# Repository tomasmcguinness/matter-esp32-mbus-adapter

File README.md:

# Matter ESP32 M-Bus Adapter

> ⚠️ **Work in progress.** This project is under active development and is not
> finished. Nothing here should be considered stable or production-ready. Expect
> breaking changes, incomplete features and rough edges.

An ESP32-C6 adapter board for wired [M-Bus](https://en.wikipedia.org/wiki/Meter-Bus)
(EN 13757) meters, with firmware examples that expose meter readings to a
[Matter](https://csa-iot.org/all-solutions/matter/) fabric over Thread.

It is built around an **ESP32-C6** (native 802.15.4 radio) and a custom PCB that
provides the M-Bus master side: the ~36 V/~24 V bus supply, the mark/space
modulator and the receive comparator, so a meter can be connected directly to the
board's M+/M- terminals.

## Repository layout

| Path | Contents |
|---|---|
| `examples/` | Firmware examples, each a standalone ESP-IDF project — see the [examples README](examples/README.md) |
| `hardware/PCB/` | KiCad schematic, PCB layout and BOM (`PCB.csv`, Mouser part numbers) |
| `tools/pcb-test/` | Standalone GPIO-only app for bringing up the M-Bus analogue circuit — see its own [README](tools/pcb-test/README.md) |
| `tools/kamstrup-403-sim/` | Raspberry Pi Pico sketch that simulates a Kamstrup MULTICAL 403 on the bus — see its own [README](tools/kamstrup-403-sim/README.md) |

## Examples

| Example | Device | Matter device type |
|---------|--------|--------------------|
| [KamstrupMultical403](examples/matter/KamstrupMultical403) | Kamstrup MULTICAL 403 heat meter | Custom Heat Meter cluster, with Flow Measurement |

Each example's README covers building, flashing, bring-up modes and the factory
reset gesture.

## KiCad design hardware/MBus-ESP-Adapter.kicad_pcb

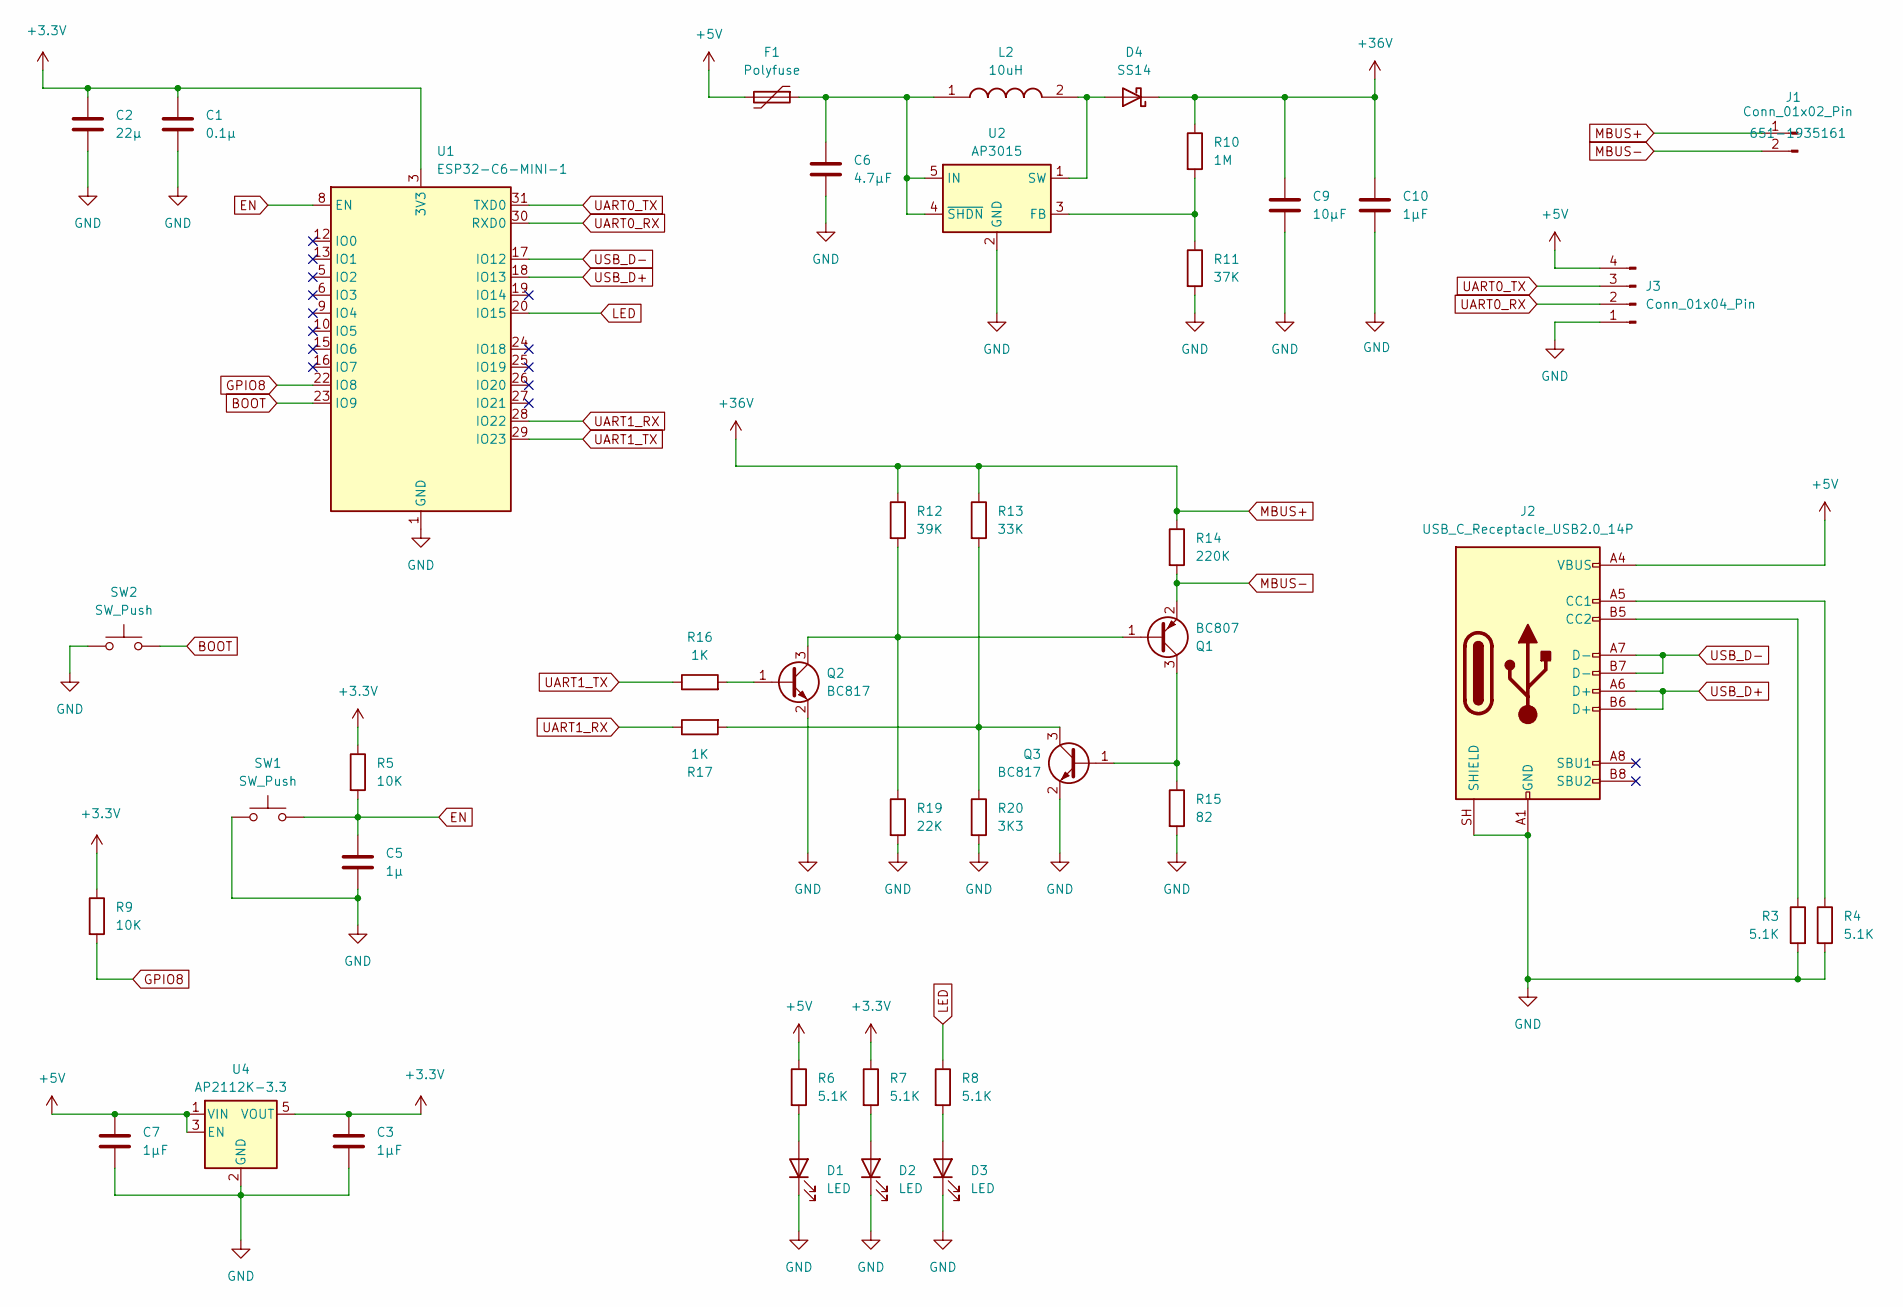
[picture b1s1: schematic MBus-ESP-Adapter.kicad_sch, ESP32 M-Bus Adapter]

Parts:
C1: 0.1µ; C_0805_2012Metric; Mouser_PN 187-CL21B104KBCNNNC
C2: 22µ; C_0805_2012Metric; Mouser_PN 963-MSASL21GBB5226MT
C3, C7: 1µF; C_0805_2012Metric; Mouser_PN 80-C0805C105J4RACLR
C5: 1µ; C_0805_2012Metric; Mouser_PN 80-C0805C105J4RACLR
C6: 4.7µF; C_1206_3216Metric; Mouser_PN 80-C1206C475K5P
C9: 10µF; C_1206_3216Metric; Mouser_PN 963-UMK316BBJ106ML-T
C10: 1µF; C_1206_3216Metric; Mouser_PN 187-CL31B105KBHNNNE
D1, D2, D3: LED; LED_0805_2012Metric; Mouser_PN 859-LTST-C171KRKT
D4: SS14; D_SMA; Mouser_PN 512-SS14
F1: Polyfuse; L_1206_3216Metric_Pad1.22x1.90mm_HandSolder; Mouser_PN 576-1206L050YR
J1: Conn_01x02_Pin; TerminalBlock_MaiXu_MX126-5.0-02P_1x02_P5.00mm; Mouser_PN 651-1935161
J2: USB_C_Receptacle_USB2.0_14P; USB_C_Receptacle_GCT_USB4105-xx-A_16P_TopMnt_Horizontal; Mouser_PN 640-USB4105-GF-A
J3: Conn_01x04_Pin; PinHeader_1x04_P2.54mm_Vertical
L2: 10uH; CR54NP221KC; Mouser_PN 851-CR54NP-100MC
Q1: BC807; SOT-23; Mouser_PN 583-BC807
Q2, Q3: BC817; SOT-23; Mouser_PN 771-BC817-25235
R3, R4, R6, R7, R8: 5.1K; R_0805_2012Metric; Mouser_PN 603-RC0805FR-075K1L
R5, R9: 10K; R_0805_2012Metric; Mouser_PN 603-RC0805FR-0710KL
R10: 1M; R_0805_2012Metric; Mouser_PN 603-RT0805FRE131ML
R11: 37K; R_0805_2012Metric; Mouser_PN 603-RT0805FRE0737K4L
R12: 39K; R_0805_2012Metric; Mouser_PN 603-RC0805FR-0739KL
R13: 33K; R_0805_2012Metric; Mouser_PN 603-RC0805FR-0733KL
R14: 220K; R_0805_2012Metric; Mouser_PN 603-RC0805FR-07220KL
R15: 82; R_0805_2012Metric; Mouser_PN 603-RC0805FR-0782RL
R16, R17: 1K; R_0805_2012Metric; Mouser_PN 603-RC0805FR-071KL
R19: 22K; R_0805_2012Metric; Mouser_PN 603-RC0805FR-0722KL
R20: 3K3; R_0805_2012Metric; Mouser_PN 603-RT0805FRE073K3L
SW1, SW2: SW_Push; SW_SPST_TS-1088-xR025; Mouser_PN 640-SWT0110020010SSA
U1: ESP32-C6-MINI-1; ESP32-C6-MINI-1U; Mouser_PN 356-ESP32-C6MINI1UH4
U2: AP3015; SOT-23-5; Mouser_PN 621-AP3015AKTR-G1
U4: AP2112K-3.3; SOT-23-5; Mouser_PN 621-AP2112K-3.3TRG1

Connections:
+3.3V: C1.1, C2.1, C3.1, R5.1, R7.1, R9.1, U1.3 (3V3), U4.5 (VOUT)
+5V: C7.1, F1.2, J2.A4 (VBUS), J2.A9 (VBUS), J2.B4 (VBUS), J2.B9 (VBUS), J3.4, R6.1, U4.1 (VIN), U4.3 (EN)
BOOT: SW2.2, U1.23 (IO9)
EN: C5.1, R5.2, SW1.2, U1.8 (EN)
GND: C1.2, C2.2, C3.2, C5.2, C6.2, C7.2, C9.2, C10.2, D1.1 (K), D2.1 (K), D3.1 (K), J2.A1 (GND), J2.A12 (GND), J2.B1 (GND), J2.B12 (GND), J2.SH (SHIELD), J3.1, Q2.2 (E), Q3.2 (E), R3.2, R4.2, R11.2, R15.2, R19.2, R20.2, SW1.1, SW2.1, U1.1 (GND), U1.2 (GND), U1.11 (GND), U1.14 (GND), U1.36 (GND), U1.37 (GND), U1.38 (GND), U1.39 (GND), U1.40 (GND), U1.41 (GND), U1.42 (GND), U1.43 (GND), U1.44 (GND), U1.45 (GND), U1.46 (GND), U1.47 (GND), U1.48 (GND), U1.49 (GND), U1.50 (GND), U1.51 (GND), U1.52 (GND), U1.53 (GND), U2.2 (GND), U4.2 (GND)
GPIO8: R9.2, U1.22 (IO8)
LED: R8.1, U1.20 (IO15)
MBUS+: C9.1, C10.1, D4.1 (K), J1.1, R10.1, R12.1, R13.1, R14.1
MBUS-: J1.2, Q1.2 (E), R14.2
unnamed: D1.2 (A), R6.2
unnamed: D2.2 (A), R7.2
unnamed: D3.2 (A), R8.2
unnamed: D4.2 (A), L2.2, U2.1 (SW)
unnamed: J2.A5 (CC1), R4.1
unnamed: J2.B5 (CC2), R3.1
unnamed: Q1.1 (B), Q2.3 (C), R12.2, R19.1
unnamed: Q1.3 (C), Q3.1 (B), R15.1
unnamed: Q2.1 (B), R16.2
unnamed: Q3.3 (C), R13.2, R17.2, R20.1
unnamed: R10.2, R11.1, U2.3 (FB)
unnamed: C6.1, F1.1, L2.1, U2.4 (~SHDN), U2.5 (IN)
UART0_RX: J3.2, U1.30 (RXD0)
UART0_TX: J3.3, U1.31 (TXD0)
UART1_RX: R17.1, U1.28 (IO22)
UART1_TX: R16.1, U1.29 (IO23)
USB_D+: J2.A6 (D+), J2.B6 (D+), U1.18 (IO13)
USB_D-: J2.A7 (D-), J2.B7 (D-), U1.17 (IO12)

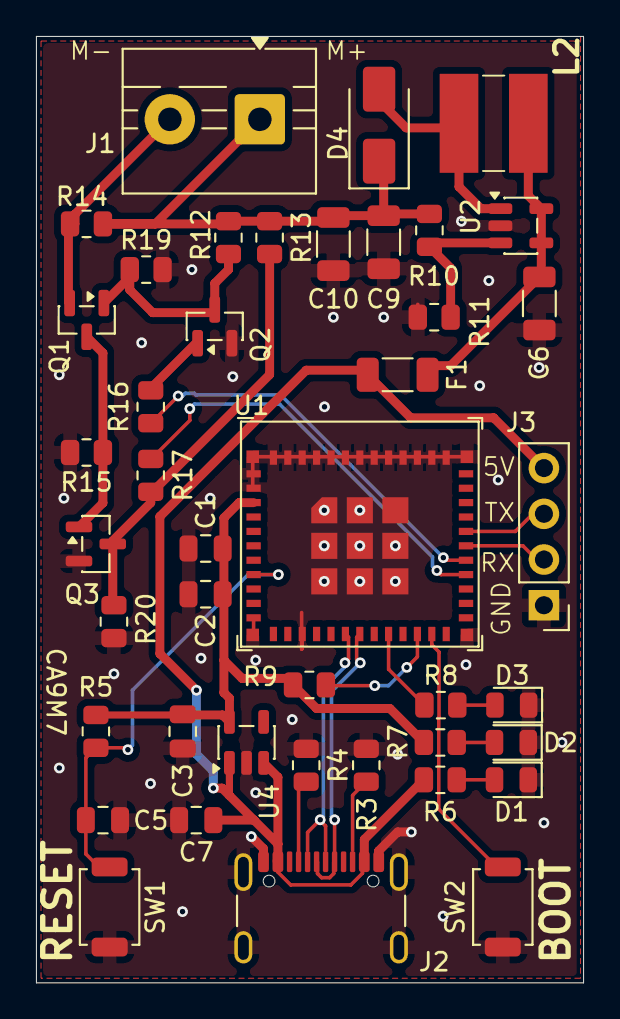
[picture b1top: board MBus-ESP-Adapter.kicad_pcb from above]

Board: 2 copper layers, 30.4 x 52.6 mm, 42 parts (0 on the bottom side), 27 nets.
